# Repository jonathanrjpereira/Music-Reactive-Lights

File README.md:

# Music Reactive LEDs
LED lights that are controlled by music levels.

**Order PCB:** 

## Electronic Components
| Qty | Component | Buy |
| ------------- | ------------- | ------------- |
| 1 | Electret Condenser Microphone |[AliExpress](http://s.click.aliexpress.com/e/bSOOMYPe) |
| 1 | BC547 PNP Transistor |[AliExpress](http://s.click.aliexpress.com/e/bpL0Irsk) |
| 1 | 10KΩ Potentiometer |[AliExpress](http://s.click.aliexpress.com/e/bR23nRuG) |
| 2 | 1KΩ Resistor |[AliExpress](http://s.click.aliexpress.com/e/bh4eqrQs) |
| 3 | 5mm LED |[AliExpress](http://s.click.aliexpress.com/e/wuFpLXS) |
| 1 | 10uF Capacitor |[AliExpress](http://s.click.aliexpress.com/e/c9FHzl5W) |
| 1 | 0.1uF (100nF) Capacitor |[AliExpress](http://s.click.aliexpress.com/e/byQG0DZW) |
| 1 | 9V Battery Holder |[AliExpress](http://s.click.aliexpress.com/e/c3jbp72Y) |
| 1 | 9V Battery |[AliExpress](http://s.click.aliexpress.com/e/bbDirGHE) |
| 1 | PCB |[AliExpress](http://s.click.aliexpress.com/e/dhgwzKY) |

| Tools | Buy |
|--|--|
|Soldering Iron|[AliExpress](http://s.click.aliexpress.com/e/E83bSJI) |
|Soldering Wire|[AliExpress](http://s.click.aliexpress.com/e/PdhB0nm) |
|Mini PCB Hand Drill + Bits|[AliExpress](http://s.click.aliexpress.com/e/b93tomjI) |

## Working

The input of a Microphone is filtered through a Low Pass Filter. The filter will only allow certain frequencies at the output. The LEDs will only react to these filtered frequencies.

**Low Pass Filter:**

A Low Pass Filter (LPF) will block all signals that are above it's Cutoff Frequency and allow only those signals that are below it's Cutoff Frequency.

The Cutoff Frequency can be set by selecting the passive components as follows: 

## Circuit

The Electret Condenser Microphone has a frequency range between 100-10,000 Hz. The 10KΩ potentiometer can be varied to change the Cutoff Frequency of the Low Pass Filter.
For example, if the pot is set to 10KΩ, the Cutoff Frequency will be equal to 159Hz. Similarly if the pot is set to 100Ω the Cutoff Frequency will be equal to 15KHz.
The transistor BC547 acts as a switch which turns the LEDs ON.

You can **Order the PCB:** 

Or you can printout the [PDF file](https://github.com/jonathanrjpereira/Music-Reactive-Lights/blob/master/img/printable.pdf) and make your own PCB using the [Iron-on method]().

## Contributing🛠
Are you an engineer or hobbyist who has a great idea for a new feature in this project? Maybe you have a good idea for a bug fix? Feel free to grab our code & schematics from Github and tinker with it. Don't forget to smash ⭐️ & the Pull Request button.

[![alt text][1.1]][1] [![alt text][2.1]][2] [![alt text][3.1]][3]

[1.1]: https://github.com/jonathanrjpereira/Social-Media-README/blob/master/youtube.png (YouTube)
[2.1]: https://github.com/jonathanrjpereira/Social-Media-README/blob/master/instagram.png (Instagram)
[3.1]: https://github.com/jonathanrjpereira/Social-Media-README/blob/master/github.png (GitHub)

[1]: https://www.youtube.com/channel/UCRW-41O1vy98KKgJRQoYzdg
[2]: https://www.instagram.com/electroguruji/
[3]: https://github.com/jonathanrjpereira

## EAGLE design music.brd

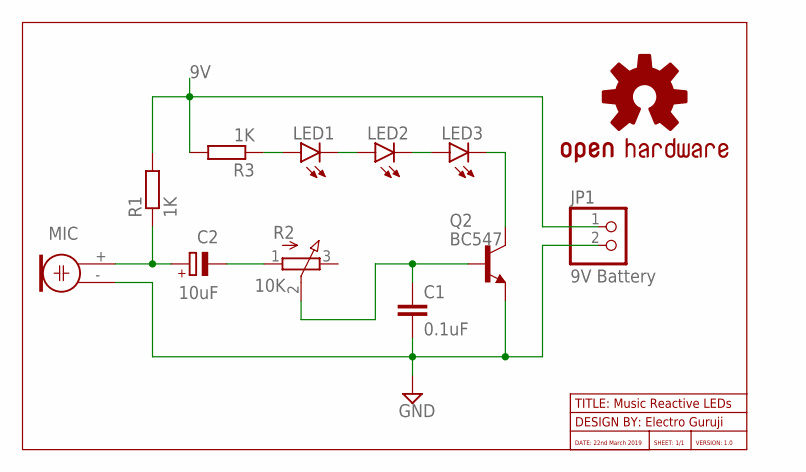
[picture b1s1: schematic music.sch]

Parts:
C1: 0.1uF; C025-050X050
C2: 10uF; E2,5-6
JP1: 9V Battery; 1X02
LED1, LED2, LED3: LED5MM
LOGO1: OSHW-LOGOMINI; OSHW-LOGO-MINI
MIC: ELECTRET; 9.7ELECTRET
Q2: BC547; TO92-CBE
R1, R3: 1K; 0207/10
R2: 10K; 3RP/1610N

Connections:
9V: JP1.1, R1.2, R3.2
GND: C1.2, JP1.2, MIC.- (1), Q2.E
unnamed: C2.+, MIC.+ (2), R1.1
unnamed: C2.-, R2.1 (A)
unnamed: C1.1, Q2.B, R2.2 (S)
unnamed: LED3.K (C), Q2.C
unnamed: LED1.A, R3.1
unnamed: LED1.K (C), LED2.A
unnamed: LED2.K (C), LED3.A

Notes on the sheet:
TITLE: Music Reactive LEDs
DESIGN BY: Electro Guruji
DATE: 22nd March 2019
SHEET: 1/1
VERSION: 1.0

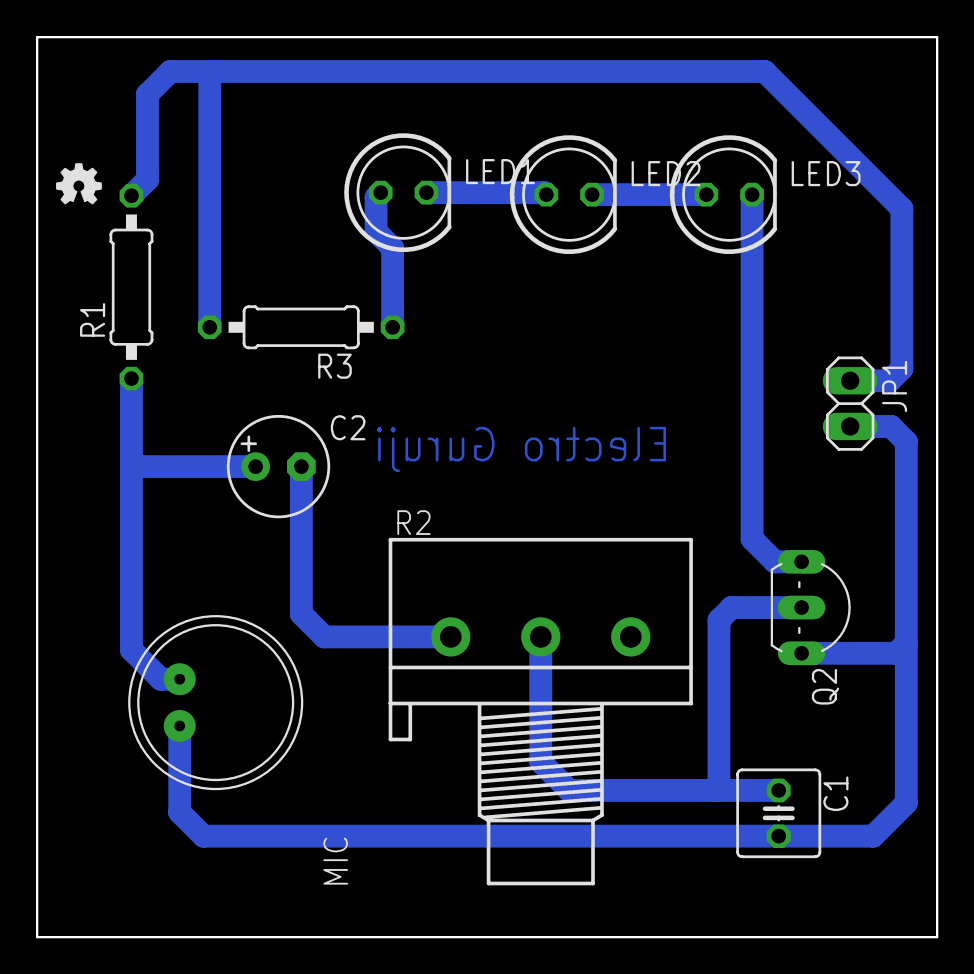
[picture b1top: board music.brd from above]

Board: 2 copper layers, 50.0 x 50.0 mm, 12 parts (0 on the bottom side), 9 nets.

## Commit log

2019-03-22 Artwork
2019-03-22 Schematic
2019-03-22 Board
2019-03-22 Printable
2019-03-22 Working + BOM
2019-03-25 eagle

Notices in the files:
parts and their libraries:
SparkFun-Aesthetics: Licensing: Creative Commons ShareAlike 4.0 International - https://creativecommons.org/licenses/by-sa/4.0
